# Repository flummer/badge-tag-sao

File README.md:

# Badge Tag SAO

Further documentation on the [hackaday.io project page for the Badge Tag SAO](https://hackaday.io/project/198165-badge-tag-nfc-sao)

Main Components:

- [NXP NT3H2211W0FTT - NTAG I2C plus 2K, NFC Forum Type 2 Tag with I2C interface](https://www.nxp.com/part/NT3H2211W0FT1)
    - [datasheet](https://www.nxp.com/docs/en/data-sheet/NT3H2111_2211.pdf)

## Designed in KiCad v8.99 (nightly)

To open the project, you will need to install a recent nightly build (og v9 or newer when released), KiCad v8 or earlier won't open this design directly.

## License

The hardware design of the `main` branch of this repository is released under the following license:

* the "Creative Commons Attribution-ShareAlike 4.0 International License"
  (CC BY-SA 4.0) full text of this license is included in the LICENSE file
  and a copy can also be found at
  [http://creativecommons.org/licenses/by-sa/4.0/](http://creativecommons.org/licenses/by-sa/4.0/)

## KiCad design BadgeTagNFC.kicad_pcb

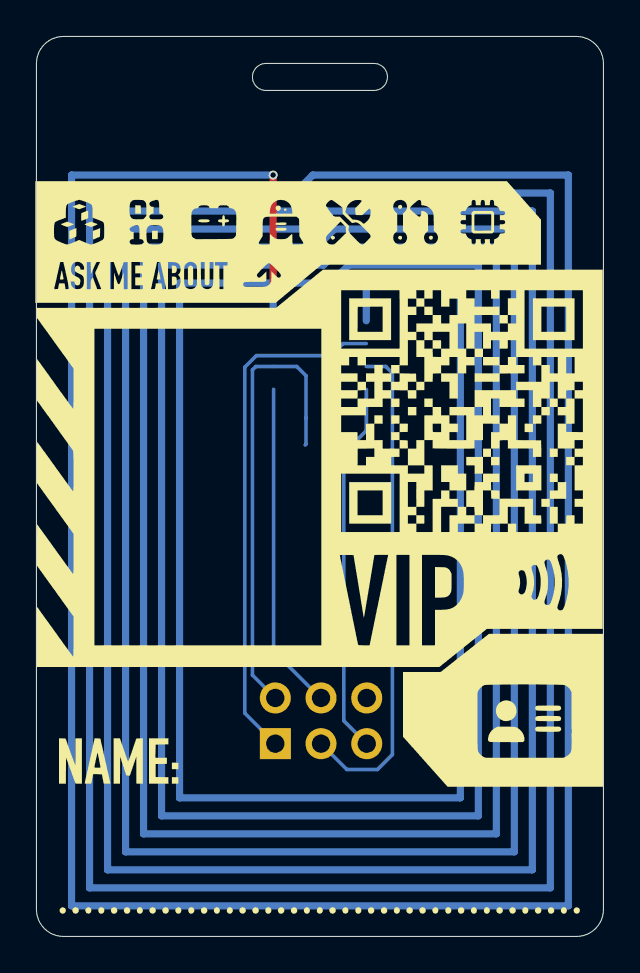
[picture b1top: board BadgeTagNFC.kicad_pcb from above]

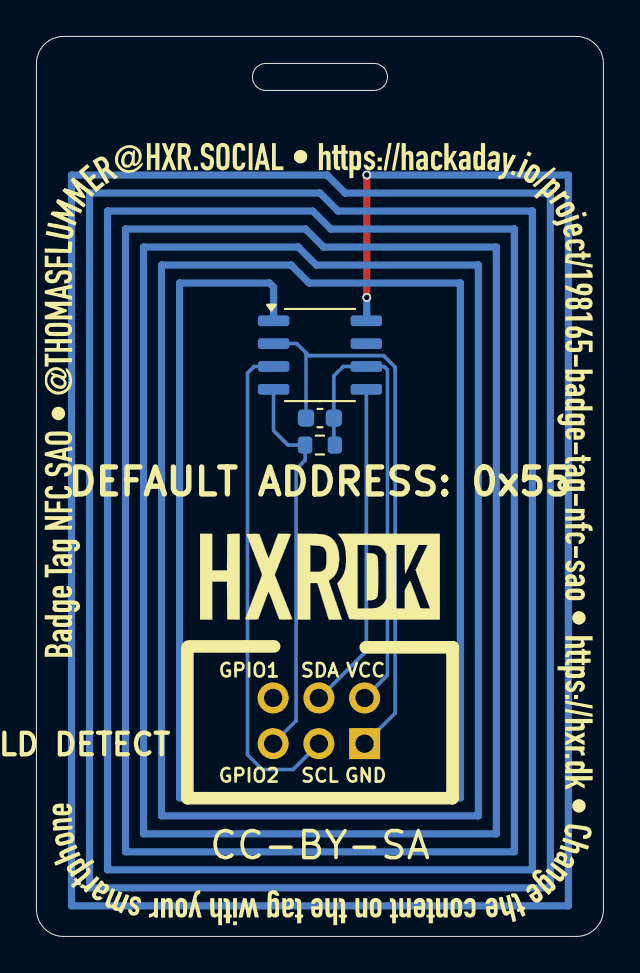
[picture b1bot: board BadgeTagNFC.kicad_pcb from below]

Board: 2 copper layers, 31.5 x 50.0 mm, 4 parts (3 on the bottom side), 6 nets.

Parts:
C1: 100nF; C_0603_1608Metric
R1: 10k; R_0603_1608Metric
U1: NT3H2x11; SO-8_3.9x4.9mm_P1.27mm
X1: Badgelife_sao_connector_v169bis; Badgelife-SAOv169-SAO-2x3

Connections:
/NTAG NFC/COIL: U1.1 (LA), U1.8 (LB)
FieldDetect: R1.2, U1.4 (FD), X1.6 (GPIO2)
GND: C1.2, U1.2 (VSS), X1.2 (GND)
SCL: U1.3 (SCL), X1.4 (SCL)
SDA: U1.5 (SDA), X1.3 (SDA)
VCC: C1.1, R1.1, U1.6 (VCC), X1.1 (VCC)

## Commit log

2024-10-15 Added documentation and license
